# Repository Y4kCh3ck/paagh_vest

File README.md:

# PAAGH VEST

The goal of the project was to create a device that can be a every sailor guardian angel. The vest detects moment when user falls overboard and starts monitoring vitals and broadcasting SOS signal over AIS protocool.

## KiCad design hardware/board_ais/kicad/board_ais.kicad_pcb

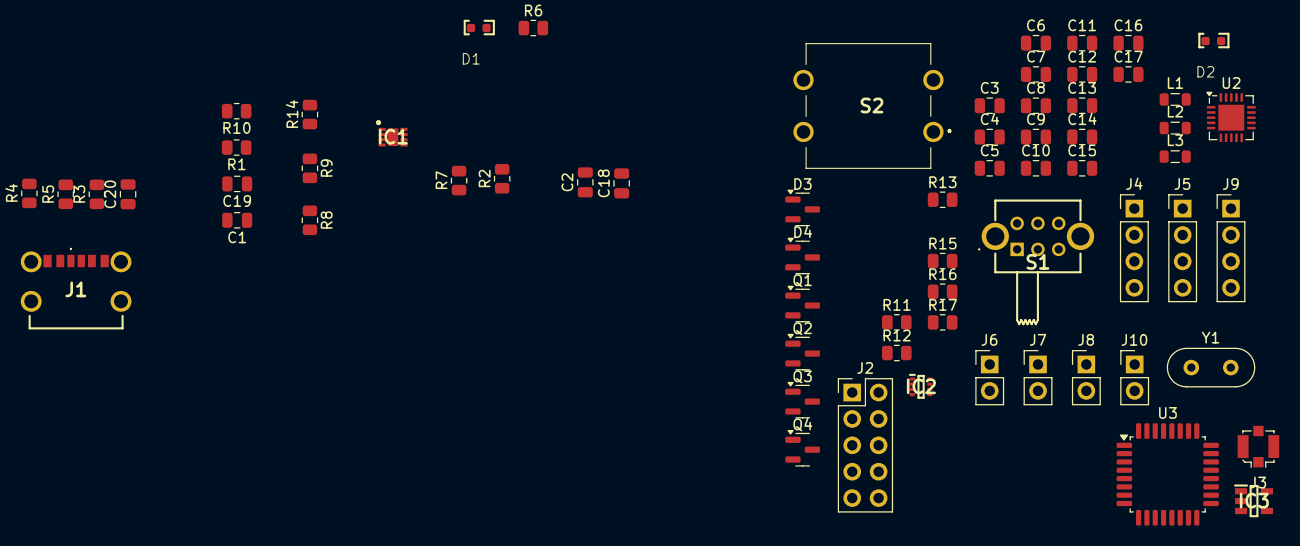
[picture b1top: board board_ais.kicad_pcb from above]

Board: 2 copper layers, 66 parts (0 on the bottom side), 56 nets, no tracks yet.

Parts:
C1, C2, C3, C14: 1u; C_0805_2012Metric
C4, C5, C6, C9: 100n; C_0805_2012Metric
C7, C15: 22p; C_0805_2012Metric
C8: 33n; C_0805_2012Metric
C10, C18, C19, C20: 10n; C_0805_2012Metric
C11: 1n; C_0805_2012Metric
C12: 1p5; C_0805_2012Metric
C13: 1p; C_0805_2012Metric
C16: 2n2; C_0805_2012Metric
C17: 4p7; C_0805_2012Metric
D1, D2: LED; nasz_zajebisty_led
D3, D4: D; SOT-23
IC1: BQ25172DSGR; SON50P200X200X80-9N
IC2: TPS2117DRLR; SOTFL50P160X60-8N
IC3: ADP160AUJZ-3.3-R7; SOT95P280X100-5N
J1: USB4125-GF-A-0190; USB4125GFA0190
J2: SWD_CONNECTOR; PinHeader_2x05_P2.54mm_Vertical
J3: UFL; U.FL_Molex_MCRF_73412-0110_Vertical
J4: I2C_CONNECTOR; PinHeader_1x04_P2.54mm_Vertical
J5: ADC_CONNECTOR; PinHeader_1x04_P2.54mm_Vertical
J6: VCC_CONNECTOR; PinHeader_1x02_P2.54mm_Vertical
J7: PETLIER_TEG; PinHeader_1x02_P2.54mm_Vertical
J8: BATTERY_CONNECTOR; PinHeader_1x02_P2.54mm_Vertical
J9: GPS_CONNECTOR; PinHeader_1x04_P2.54mm_Vertical
J10: PETLIER_TEC; PinHeader_1x02_P2.54mm_Vertical
L1: 8n2; L_0805_2012Metric
L2: 3n9; L_0805_2012Metric
L3: 2n7; L_0805_2012Metric
Q1, Q2, Q3, Q4: PMOS; SOT-23
R1: 600; R_0805_2012Metric
R2, R7: 15k; R_0805_2012Metric
R3, R17: 1M; R_0805_2012Metric
R4, R5: 5.11k; R_0805_2012Metric
R6, R10, R12, R14, R16: 10k; R_0805_2012Metric
R8: 1k; R_0805_2012Metric
R9: 2k; R_0805_2012Metric
R11, R15: 22k; R_0805_2012Metric
R13: 2k2; R_0805_2012Metric
S1: ON/OFF_SWITCH; SLW8269475ARAD
S2: FSM100
U2: nRF24L01P; QFN-20-1EP_4x4mm_P0.5mm_EP2.5x2.5mm
U3: STM32L071KBT6; LQFP-32_7x7mm_P0.8mm
Y1: 16MHz; Crystal_HC52-U_Vertical

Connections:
3.3V: C3.1, C4.1, C5.1, C6.1, C10.1, C11.1, C14.1, IC3.5 (VOUT), J2.1, J6.1, Q1.3 (S), Q2.3 (S), Q3.3 (S), R11.1, S2.2, U2.7 (VDD), U2.15 (VDD), U2.18 (VDD), U3.1 (VDD), U3.5 (VDDA), U3.17 (VDD), U3.19 (PA9)
+5V: C1.1, C19.1, IC1.1 (IN), IC2.3 (VIN1), IC2.5 (MODE), J1.A9 (VBUS_1), J1.B9 (VBUS_2), R6.2, R8.1, R14.1
ADC_EN: Q3.2 (G), U3.22 (PA12)
ADC_IN0: J5.1, U3.6 (PA0)
ADC_IN1: J5.2, U3.7 (PA1)
BAT: C2.1, C18.1, IC1.8 (OUT), S1.4 (NC_2)
GND: C1.2, C2.2, C3.2, C4.2, C5.2, C6.2, C7.2, C8.2, C9.2, C10.2, C11.2, C13.2, C14.2, C15.2, C16.2, C17.2, C18.2, C19.2, C20.2, IC1.4 (GND_1), IC1.9 (GND_2), IC2.1 (GND), IC3.2 (GND), J1.A12 (GND_1), J1.B12 (GND_2), J2.3, J2.5, J2.9, J4.3, J5.3, J6.2, J7.1, J8.1, J9.3, J10.1, R1.2, R2.2, R3.2, R4.2, R5.2, R7.2, R9.2, R10.2, R12.2, R13.2, R16.2, R17.2, S1.MH1, U2.8 (VSS), U2.14 (VSS), U2.17 (VSS), U2.20 (VSS), U3.16 (VSS), U3.32 (VSS)
GPS_EN: Q1.2 (G), U3.21 (PA11)
HEATER_EN: Q4.2 (G), U3.25 (PA15)
I2C1_SCL: J4.2, U3.29 (PB6)
I2C1_SDA: J4.1, U3.30 (PB7)
I2C_EN: Q2.2 (G), U3.20 (PA10)
LPUART_RX: J9.2, U3.9 (PA3)
LPUART_TX: J9.1, U3.8 (PA2)
NRF_ANT1: L1.2, L3.1, U2.12 (ANT1)
NRF_ANT2: L1.1, L2.1, U2.13 (ANT2)
NRF_CE: U2.1 (CE), U3.27 (PB4)
NRF_IRQ: U2.6 (IRQ), U3.28 (PB5)
NRF_VDD_PA: C16.1, C17.1, L3.2, U2.11 (VDD_PA)
NRST: C9.1, J2.10, U3.4 (NRST)
unnamed: C12.1, L2.2
unnamed: C20.1, J1.MH1, J1.MH4, R3.1
unnamed: D1.2 (A), R6.1
unnamed: D1.1 (K), IC1.5 (STAT)
unnamed: D2.2 (A), U3.18 (PA8)
unnamed: D2.1 (K), R13.1
unnamed: D3.1 (K), D4.1 (K), Q4.1 (D)
unnamed: IC1.2 (ISET), R1.1
unnamed: IC1.6 (TMR), R7.1
unnamed: IC1.3 (TS), R10.1
unnamed: IC1.7 (VSET), R2.1
unnamed: IC2.4 (PR1), R8.2, R9.1
unnamed: J1.A5 (CC1), R4.1
unnamed: J1.B5 (CC2), R5.1
unnamed: C13.1, J3.2 (Ext)
unnamed: C12.2, J3.1 (In)
unnamed: J4.4, Q2.1 (D)
unnamed: J5.4, Q3.1 (D)
unnamed: J9.4, Q1.1 (D)
unnamed: R17.1, S2.1
unnamed: C8.1, U2.19 (DVDD)
unnamed: R11.2, U2.16 (IREF)
unnamed: C7.1, R15.1, U2.10 (XC1), Y1.1
unnamed: C15.1, R15.2, U2.9 (XC2), Y1.2
unnamed: R12.1, U3.31 (BOOT0)
ON/OFF_OUT: IC2.6 (VIN2), S1.2 (COM_1)
PA4: R16.1, U3.2 (PC14), U3.3 (PC15), U3.10 (PA4), U3.14 (PB0), U3.15 (PB1), U3.26 (PB3)
PETLIER_TEC: J10.2, Q4.3 (S)
PETLIER_TEG: D4.2 (A), J7.2
POWER_FOR_HEATER: D3.2 (A), IC2.7 (VOUT_2), IC3.1 (VIN), IC3.3 (EN)
POWER_STAT: IC2.8 (ST), R14.2
SPI1_MISO: U2.5 (MISO), U3.12 (PA6)
SPI1_MOSI: U2.4 (MOSI), U3.13 (PA7)
SPI1_SCK: U2.3 (SCK), U3.11 (PA5)
SWCLK: J2.4, U3.24 (PA14)
SWDIO: J2.2, U3.23 (PA13)

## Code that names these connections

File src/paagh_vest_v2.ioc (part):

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Mcu.Name=STM32L071K(B-Z)Tx
Mcu.Package=LQFP32
Mcu.UserName=STM32L071KBTx
PA0.Mode=IN0
PA0.Signal=ADC_IN0
PA1.GPIOParameters=GPIO_Label
PA1.GPIO_Label=NRF24_CSN
PA1.Signal=GPIO_Output
PA10.GPIOParameters=GPIO_Label
PA10.GPIO_Label=I2C_EN
PA10.Signal=GPIO_Output
PA11.GPIOParameters=GPIO_Label
PA11.GPIO_Label=GPS_EN
PA11.Signal=GPIO_Output
PA12.GPIOParameters=GPIO_Label
PA12.GPIO_Label=ADC_EN
PA12.Signal=GPIO_Output
PA13.Mode=Serial_Wire
PA13.Signal=SYS_SWDIO
PA14.Mode=Serial_Wire
PA14.Signal=SYS_SWCLK
PA15.GPIOParameters=GPIO_Label
PA15.GPIO_Label=HEATER_EN
PA15.Signal=GPIO_Output
PA2.Mode=Asynchronous
PA2.Signal=LPUART1_TX
PA3.Mode=Asynchronous
PA3.Signal=LPUART1_RX
PA5.Mode=Full_Duplex_Master
PA5.Signal=SPI1_SCK
PA6.Mode=Full_Duplex_Master
PA6.Signal=SPI1_MISO
PA7.Mode=Full_Duplex_Master
PA7.Signal=SPI1_MOSI
PA8.GPIOParameters=GPIO_Label
PA8.GPIO_Label=USER_LED
PA8.Signal=GPIO_Output
PA9.GPIOParameters=GPIO_Label
PA9.GPIO_Label=USER_BUTTON
PA9.Signal=GPIO_Input
PB4.GPIOParameters=GPIO_Label
PB4.GPIO_Label=NRF24_CE
PB4.Signal=GPIO_Output
PB5.GPIOParameters=GPIO_Label
PB5.GPIO_Label=NRF24_IRQ
PB5.Signal=GPXTI5
PB6.Mode=I2C
PB6.Signal=I2C1_SCL
PB7.Mode=I2C
PB7.Signal=I2C1_SDA
RCC.SYSCLKFreq_VALUE=32000000
RCC.SYSCLKSource=RCC_SYSCLKSOURCE_PLLCLK
board=custom

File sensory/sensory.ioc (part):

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Mcu.Name=STM32L053R(6-8)Tx
Mcu.Package=LQFP64
Mcu.UserName=STM32L053R8Tx
PA0.Mode=IN0
PA0.Signal=ADC_IN0
PA10.Mode=Asynchronous
PA10.Signal=USART1_RX
PA13.GPIOParameters=GPIO_Label
PA13.GPIO_Label=TMS
PA13.Mode=Serial_Wire
PA13.Signal=SYS_SWDIO
PA14.GPIOParameters=GPIO_Label
PA14.GPIO_Label=TCK
PA14.Mode=Serial_Wire
PA14.Signal=SYS_SWCLK
PA2.GPIOParameters=GPIO_Label
PA2.GPIO_Label=USART_TX
PA2.Mode=Asynchronous
PA2.Signal=USART2_TX
PA3.GPIOParameters=GPIO_Label
PA3.GPIO_Label=USART_RX
PA3.Mode=Asynchronous
PA3.Signal=USART2_RX
PA4.Mode=NSS_Signal_Hard_Input
PA4.Signal=SPI1_NSS
PA5.GPIOParameters=GPIO_Label
PA5.GPIO_Label=LD2 [Green Led]
PA5.Signal=GPIO_Output
PA6.Mode=Full_Duplex_Master
PA6.Signal=SPI1_MISO
PA7.Mode=Full_Duplex_Master
PA7.Signal=SPI1_MOSI
PA9.Mode=Asynchronous
PA9.Signal=USART1_TX
PB3.Mode=Full_Duplex_Master
PB3.Signal=SPI1_SCK
PB6.Mode=I2C
PB6.Signal=I2C1_SCL
PB7.Mode=I2C
PB7.Signal=I2C1_SDA
PC13.GPIOParameters=GPIO_Label,GPIO_ModeDefaultEXTI
PC13.GPIO_Label=B1 [Blue PushButton]
PC13.GPIO_ModeDefaultEXTI=GPIO_MODE_IT_FALLING
PC13.Signal=GPXTI13
PC14-OSC32_IN.Mode=LSE-External-Oscillator
PC14-OSC32_IN.Signal=RCC_OSC32_IN
PC15-OSC32_OUT.Mode=LSE-External-Oscillator
PC15-OSC32_OUT.Signal=RCC_OSC32_OUT
PC4.Mode=Asynchronous
PC4.Signal=LPUART1_TX
PC5.Mode=Asynchronous
PC5.Signal=LPUART1_RX
PC6.GPIOParameters=GPIO_Label
PC6.GPIO_Label=NRF24_CSN
PC6.Signal=GPIO_Output
PC7.GPIOParameters=GPIO_Label
PC7.GPIO_Label=NRF24_CE
PC7.Signal=GPIO_Output
PC8.GPIOParameters=GPIO_Label
PC8.GPIO_Label=NRF24_IRQ
PC8.Signal=GPXTI8
PH0-OSC_IN.Mode=HSE-External-Clock-Source
PH0-OSC_IN.Signal=RCC_OSC_IN
PH1-OSC_OUT.Signal=RCC_OSC_OUT
RCC.HSE_VALUE=8000000
RCC.SYSCLKFreq_VALUE=32000000
RCC.SYSCLKSource=RCC_SYSCLKSOURCE_PLLCLK
board=NUCLEO-L053R8
boardIOC=true

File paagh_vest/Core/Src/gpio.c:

/* USER CODE BEGIN Header */
/**
  ******************************************************************************
  * @file    gpio.c
  * @brief   This file provides code for the configuration
  *          of all used GPIO pins.
  ******************************************************************************
  * @attention
  *
  * Copyright (c) 2024 STMicroelectronics.
  * All rights reserved.
  *
  * This software is licensed under terms that can be found in the LICENSE file
  * in the root directory of this software component.
  * If no LICENSE file comes with this software, it is provided AS-IS.
  *
  ******************************************************************************
  */
/* USER CODE END Header */

/* Includes ------------------------------------------------------------------*/
#include "gpio.h"

/* USER CODE BEGIN 0 */

/* USER CODE END 0 */

/*----------------------------------------------------------------------------*/
/* Configure GPIO                                                             */
/*----------------------------------------------------------------------------*/
/* USER CODE BEGIN 1 */

/* USER CODE END 1 */

/** Configure pins as
        * Analog
        * Input
        * Output
        * EVENT_OUT
        * EXTI
        * Free pins are configured automatically as Analog (this feature is enabled through
        * the Code Generation settings)
*/
void MX_GPIO_Init(void)
{

  GPIO_InitTypeDef GPIO_InitStruct = {0};

  /* GPIO Ports Clock Enable */
  __HAL_RCC_GPIOC_CLK_ENABLE();
  __HAL_RCC_GPIOA_CLK_ENABLE();
  __HAL_RCC_GPIOB_CLK_ENABLE();

  /*Configure GPIO pin Output Level */
  HAL_GPIO_WritePin(GPIOA, NRF24_CSN_Pin|USER_LED_Pin|I2C_EN_Pin|GPS_EN_Pin
                          |ADC_EN_Pin, GPIO_PIN_RESET);

  /*Configure GPIO pin Output Level */
  HAL_GPIO_WritePin(NRF24_CE_GPIO_Port, NRF24_CE_Pin, GPIO_PIN_RESET);

  /*Configure GPIO pins : PC14 PC15 */
  GPIO_InitStruct.Pin = GPIO_PIN_14|GPIO_PIN_15;
  GPIO_InitStruct.Mode = GPIO_MODE_ANALOG;
  GPIO_InitStruct.Pull = GPIO_NOPULL;
  HAL_GPIO_Init(GPIOC, &GPIO_InitStruct);

  /*Configure GPIO pins : PAPin PAPin PAPin PAPin
                           PAPin */
  GPIO_InitStruct.Pin = NRF24_CSN_Pin|USER_LED_Pin|I2C_EN_Pin|GPS_EN_Pin
                          |ADC_EN_Pin;
  GPIO_InitStruct.Mode = GPIO_MODE_OUTPUT_PP;
  GPIO_InitStruct.Pull = GPIO_NOPULL;
  GPIO_InitStruct.Speed = GPIO_SPEED_FREQ_LOW;
  HAL_GPIO_Init(GPIOA, &GPIO_InitStruct);

  /*Configure GPIO pins : PA4 PA15 */
  GPIO_InitStruct.Pin = GPIO_PIN_4|GPIO_PIN_15;
  GPIO_InitStruct.Mode = GPIO_MODE_ANALOG;
  GPIO_InitStruct.Pull = GPIO_NOPULL;
  HAL_GPIO_Init(GPIOA, &GPIO_InitStruct);

  /*Configure GPIO pins : PB0 PB1 PB3 PB5 */
  GPIO_InitStruct.Pin = GPIO_PIN_0|GPIO_PIN_1|GPIO_PIN_3|GPIO_PIN_5;
  GPIO_InitStruct.Mode = GPIO_MODE_ANALOG;
  GPIO_InitStruct.Pull = GPIO_NOPULL;
  HAL_GPIO_Init(GPIOB, &GPIO_InitStruct);

  /*Configure GPIO pin : PtPin */
  GPIO_InitStruct.Pin = USER_BUTTON_Pin;
  GPIO_InitStruct.Mode = GPIO_MODE_INPUT;
  GPIO_InitStruct.Pull = GPIO_NOPULL;
  HAL_GPIO_Init(USER_BUTTON_GPIO_Port, &GPIO_InitStruct);

  /*Configure GPIO pin : PtPin */
  GPIO_InitStruct.Pin = NRF24_CE_Pin;
  GPIO_InitStruct.Mode = GPIO_MODE_OUTPUT_PP;
  GPIO_InitStruct.Pull = GPIO_NOPULL;
  GPIO_InitStruct.Speed = GPIO_SPEED_FREQ_LOW;
  HAL_GPIO_Init(NRF24_CE_GPIO_Port, &GPIO_InitStruct);

}

/* USER CODE BEGIN 2 */

/* USER CODE END 2 */

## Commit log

2024-04-05 kicad project init
2024-04-05 LT1512_schematic
2024-04-05 kicad board init
2024-04-05 Added extra components
2024-04-05 BQ added:
2024-04-05 Design improvements
2024-04-05 added battery charger
2024-04-06 init
2024-04-07 Updated schematics
2024-04-09 Added footprints
2024-04-09 Minor changer
2024-04-09 moved AHT20 reading to timer interrupt
2024-04-11 added heart rate dma readings
2024-04-17 layout ongoing
2024-04-28 DONE
2024-04-28 DONEv2
2024-05-22 added nRF24 lib
2024-06-09 Cleaned up
2024-06-09 Updated .gitignore
2024-06-09 ble ble ble
2024-06-09 added cubeMX project
2024-06-09 included libs
2024-06-09 debugging works
2024-06-10 Added FSM template
2024-06-10 added pins
2024-06-10 Changed buildsystem to Make
2024-06-10 ble ble
2024-06-10 gitignore change
2024-06-10 Created App directory
2024-06-10 Added sensor's drivers
2024-06-11 Added github workflow
2024-06-11 Rename c-cpp.yml to main.yml
2024-06-11 Created github workflow
    * Added github workflow
    * Rename c-cpp.yml to main.yml
    * Update main.yml
2024-06-11 added libs to vsc build:
2024-06-11 .ioc update
2024-06-11 added heater enabler
2024-06-11 Added func def in pv_pm.c
2024-06-11 Clean up
2024-06-11 Power Manager module (#3)
    * Added func def in pv_pm.c
    * Clean up
2024-06-11 Added sensors wrapper
2024-06-11 nRF now in dynamic payload, doesnt work still, uart works kinda
2024-06-11 PushTry
2024-06-11 Averaging temperature and humidity done
2024-06-11 Averaging again
2024-06-11 temp and humidity works; timer doesnt work for now
2024-06-11 Added button reading
2024-06-11 Averaging fix (#5)
2024-06-11 Button added, it is building up
2024-06-12 added heart beat array
2024-06-12 bleble
2024-06-12 added App folder
2024-06-12 Add files via upload
    pulse oximeter ale nie dziala
2024-06-12 .settings/.keep
2024-06-13 Add pulse caluclation algorithm
2024-06-13 added pulse calc
2024-06-13 added terminal prints in app
2024-06-13 moved all non-autogenerated files to App folders
2024-06-13 cleaned files
2024-06-13 cleared up
2024-06-14 cleared files
2024-06-14 final clear
2024-06-14 Merged changes from software branch
2024-06-14 Fixed directory structure
2024-06-14 added pulsoximeter
2024-06-14 Added pulseoximeter
2024-06-14 Button, build working
2024-06-14 Merge changes from software branch (#9)
    * Merged changes from software branch
    * Fixed directory structure
    * Added pulseoximeter
2024-06-14 Conflicts
2024-06-21 Update README.md (#14)
